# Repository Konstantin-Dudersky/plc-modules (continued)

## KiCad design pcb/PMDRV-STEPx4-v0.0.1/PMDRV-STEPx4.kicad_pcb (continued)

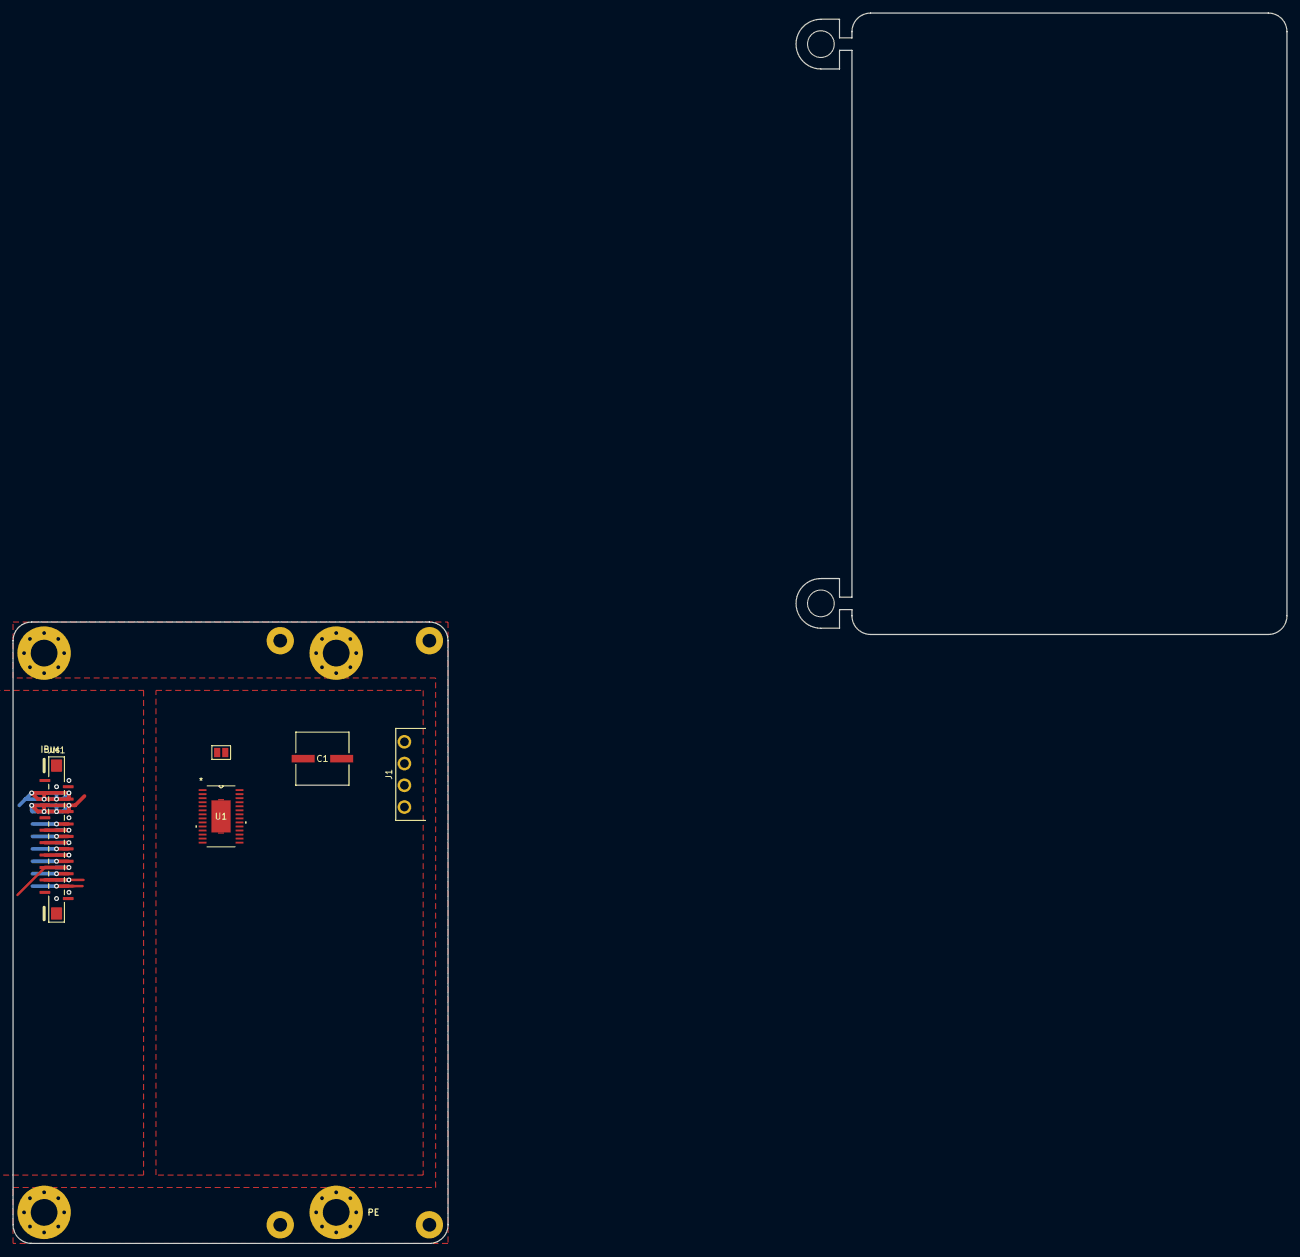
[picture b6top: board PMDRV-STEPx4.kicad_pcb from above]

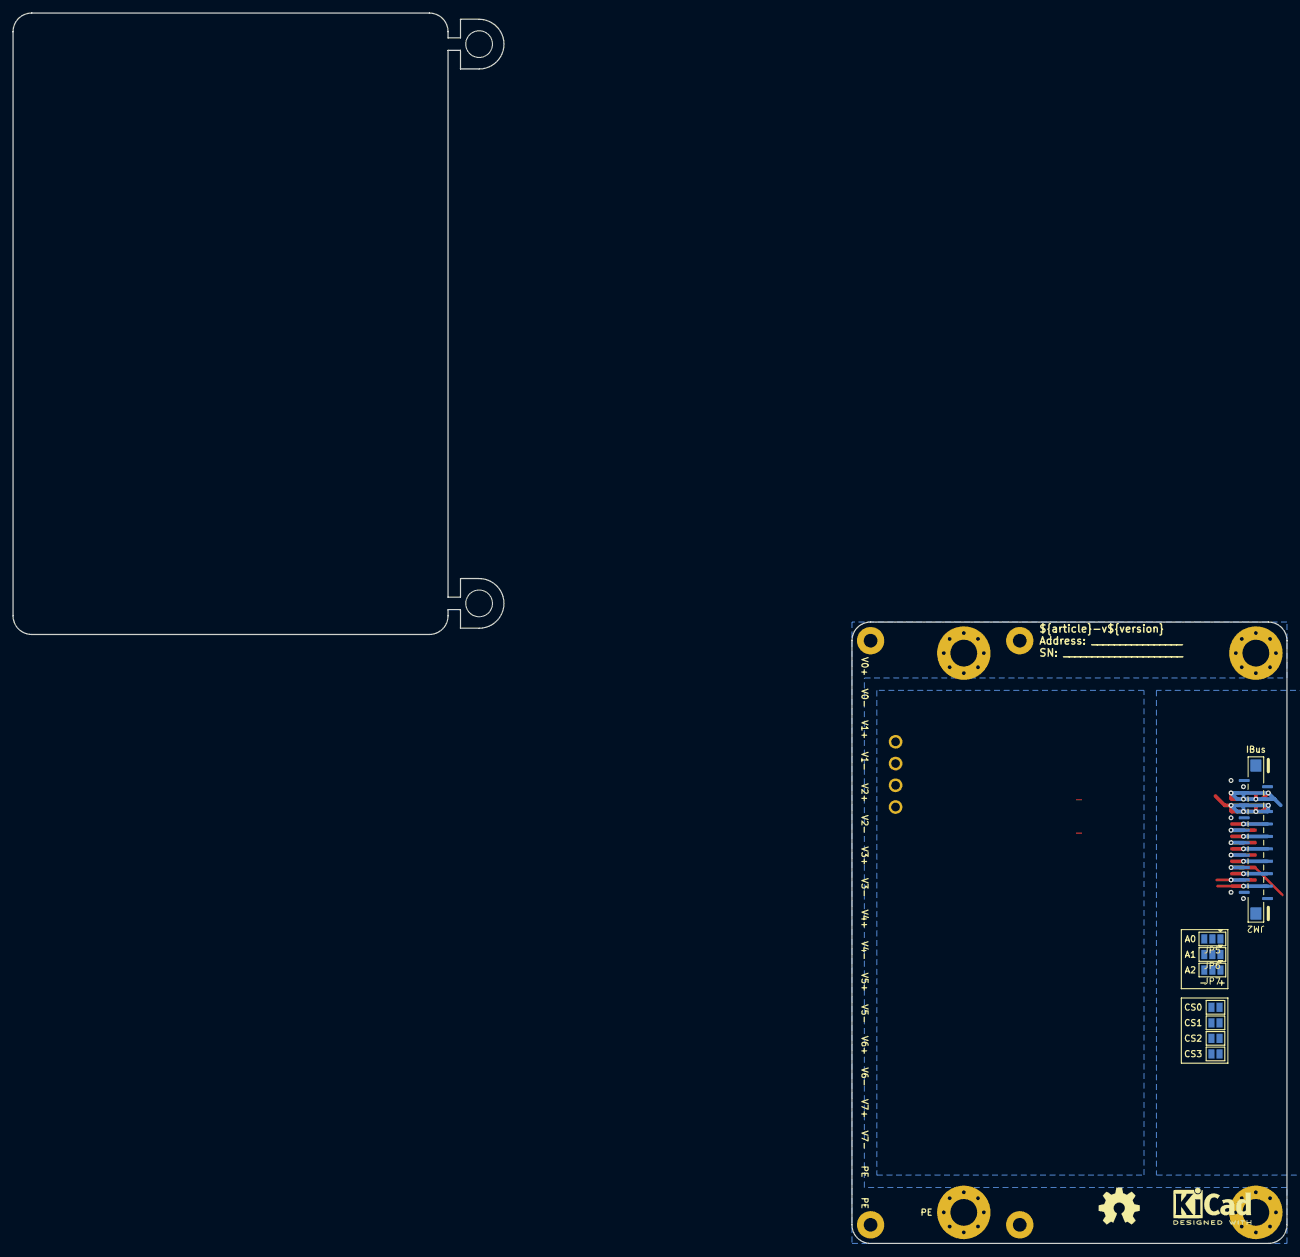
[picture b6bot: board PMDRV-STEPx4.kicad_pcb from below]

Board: 2 copper layers, 70.0 x 100.0 mm, 20 parts (10 on the bottom side), 15 nets.

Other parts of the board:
kicad_logo: KiCad-Logo2_5mm_SilkScreen
oshw_logo: OSHW-Symbol_6.7x6mm_SilkScreen

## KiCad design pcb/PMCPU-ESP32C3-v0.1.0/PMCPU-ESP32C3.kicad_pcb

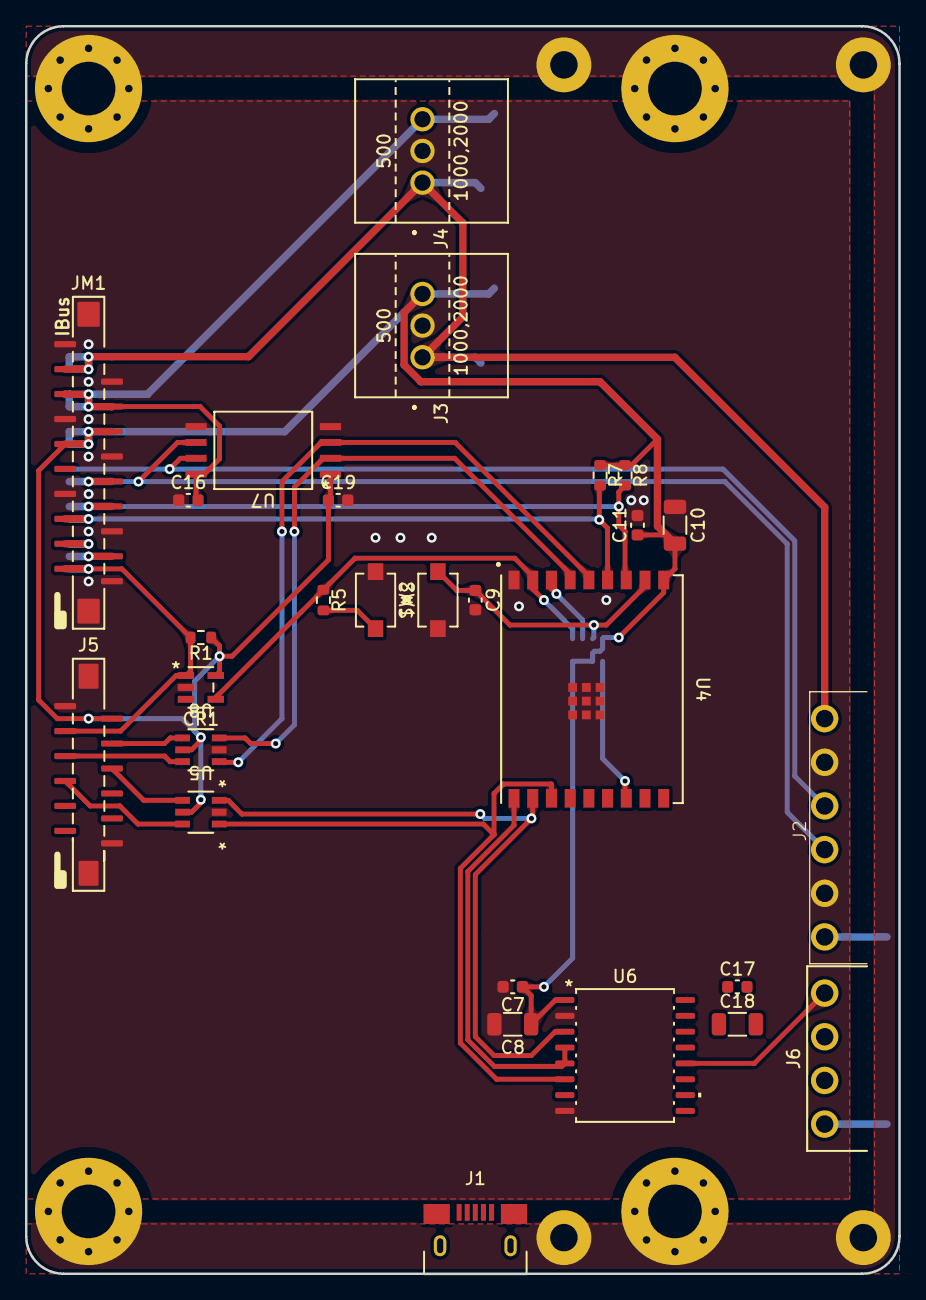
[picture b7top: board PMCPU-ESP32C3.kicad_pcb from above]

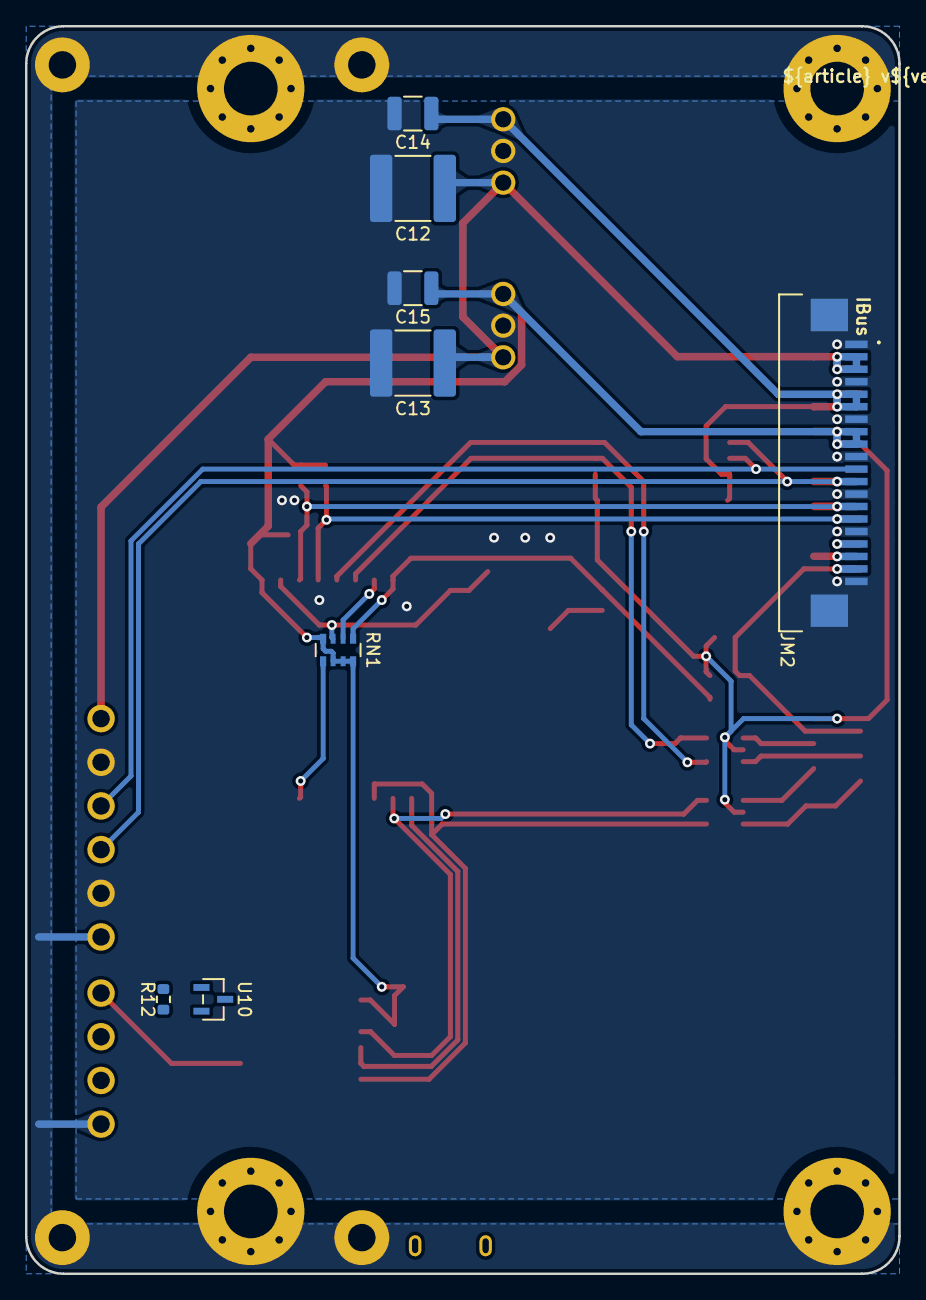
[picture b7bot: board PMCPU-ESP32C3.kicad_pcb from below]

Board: 2 copper layers, 70.0 x 100.0 mm, 43 parts (10 on the bottom side), 32 nets.

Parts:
C7, C16, C17, C19: 100nF; C_0603_1608Metric
C8, C10, C18: 10uF; C_1206_3216Metric
C9, C11: 1uF; C_0603_1608Metric
C12, C13: 22uF; C_2220_5750Metric
C14, C15: 22uF; C_1210_3225Metric
CR1: STWD100NYWY3F; SOT23-5L_STM
H1, H2, H3, H4: M4; MountingHole_4.3mm_M4_Pad_Via
J1: U254-051T-4BH83-S1S; CONN5_H83-S1S_XKB
J2: 15EDGRC-3.5-06P
J3: K7803-2000R3; K7805-2000R3
J4: K7805-2000R3
J5: AFA11-S12GLA-00
J6: 15EDGRC-3.5-04P
JM1: AFA07-S20FCC-00; AFA11-S20GLA-00
JM2: AFA07-S20FCC-00; AFA07S20FCA00
R1: 10k; R_0603_1608Metric
R5: 330R; R_0603_1608Metric
R7, R8: 3k3; R_0603_1608Metric
R12: 120R; R_0603_1608Metric
RN1: 10k; R_Array_Convex_4x0603
SP1: PMLED-xx-v0.0.3
SW1, SW2: Button; SW_TS-1088_XNP-M
U4: ESP32-C3-WROOM-02U-N4; ESP32-C3-WROOM-02U_EXP
U5, U8: SN74LVC2G14DBVR; DBV6-M
U6: CA-IS3098W; SOIC16-WBW_CLG
U7: CA-IS3050G; SOIC8_CA-IS305_CLG
U10: CDSOT23-SM712; SOT_SM712
kicad_logo: KiCad-Logo2_5mm_SilkScreen
oshw_logo: OSHW-Symbol_6.7x6mm_SilkScreen

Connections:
+3.3V_EXT_RS485: C17.1, C18.1, U6.16 (VISO)
/CAN_RX: U4.6 (IO7), U7.2 (RXD), U8.3 (2A)
/CAN_RX_LED: J5.4, U8.4 (2Y)
/CAN_TX: U4.5 (IO6), U7.3 (TXD), U8.1 (1A)
/CAN_TX_LED: J5.5, U8.6 (1Y)
/EN: C9.1, RN1.3 (R3.1), SW2.2, U4.2 (EN)
/IBUS_CAN_H: J2.4, JM1.11, JM2.11, U7.7 (CANH)
/IBUS_CAN_L: J2.3, JM1.12 (Pin_11), JM2.12 (Pin_11), U7.6 (CANL)
/IBUS_I2C_SCL: JM1.15 (Pin_11), JM2.15 (Pin_11), R7.2, U4.4 (IO5)
/IBUS_I2C_SDA: JM1.14 (Pin_11), JM2.14 (Pin_11), R8.2, U4.3 (IO4)
/IBUS_RST: CR1.1 (*WDO), J5.3, JM1.19 (Pin_11), JM2.19 (Pin_11), R1.2
/RS485-A: J6.4, R12.2, U6.12 (A), U10.1
/RS485-B: J6.3, R12.1, U6.13 (B), U10.2
/UART_RTS: U4.10 (IO10), U6.4 (RE), U6.5 (DE)
/UART_RX: U4.11 (RXD_(IO20)), U5.3 (2A), U6.3 (RO)
/UART_RX_LED: J5.6, U5.4 (2Y)
/UART_TX: U4.12 (TXD_(IO21)), U5.1 (1A), U6.6 (DI)
/UART_TX_LED: J5.7, U5.6 (1Y)
/USB_D+: J1.3 (D+), U4.14 (IO19_(USB_D+))
/USB_D-: J1.2 (D-), U4.13 (IO18_(USB_D-))
/WDT: CR1.4 (WDI), R5.1, RN1.1 (R1.1), U4.8 (IO9)
GND_EXT_RS485: C17.2, C18.2, J6.2, U6.9 (GNDB), U6.10 (SEL), U6.15 (GNDB), U10.3
IBUS_3V3: C7.1, C8.1, C10.2, C11.1, C15.1, C19.1, CR1.5 (VCC), J3.3 (+VO), J5.2, JM1.8, JM1.9, JM2.8, JM2.9, R1.1, R7.1, R8.1, RN1.4 (R4.1), RN1.6 (R3.2), RN1.7 (R2.2), RN1.8 (R1.2), U4.1 (3V3), U5.5 (VCC), U6.1 (VDD), U7.1 (VCC1), U8.5 (VCC)
IBUS_5V: C14.1, C16.2, J4.3 (+VO), JM1.5, JM1.6, JM2.5, JM2.6, U7.8 (VCC2)
IBUS_24V: C12.1, C13.1, J2.6, J3.1 (VIN), J4.1 (VIN), JM1.2, JM1.3, JM2.2, JM2.3
IBUS_CAN_GND: C7.2, C8.2, C9.2, C10.1, C11.2, C12.2, C13.2, C14.2, C15.2, C16.1, C19.2, CR1.2 (GND), J1.5 (GND), J2.2, J2.5, J3.2 (GND), J4.2 (GND), J5.1, J5.12 (Pin_11), J5.MP1 (Pin_11), J5.MP2 (Pin_11), JM1.1, JM1.4, JM1.7, JM1.10, JM1.13 (Pin_11), JM1.16 (Pin_11), JM1.20 (Pin_11), JM1.MP1 (Pin_11), JM1.MP2 (Pin_11), JM2.1, JM2.4, JM2.7, JM2.10, JM2.13 (Pin_11), JM2.16 (Pin_11), JM2.20 (Pin_11), JM2.MP1 (Pin_11), JM2.MP2 (Pin_11), SW1.1, SW2.1, U4.9 (GND), U4.EPAD, U5.2 (GND), U6.2 (GNDA), U6.8 (GNDA), U7.4 (GND1), U7.5 (GND2), U8.2 (GND)
unnamed: JM1.17 (Pin_11), JM2.17 (Pin_11)
unnamed: JM1.18 (Pin_11), JM2.18 (Pin_11)
unnamed: R5.2, SW1.2
unnamed: RN1.2 (R2.1), U4.7 (IO8)
unnamed: RN1.5 (R4.2), U4.16 (IO2)
PE: H1.1 (1_1), H2.1 (1_1), H3.1 (1_1), H4.1 (1_1), J2.1, J6.1, SP1.PE (PE_PE)

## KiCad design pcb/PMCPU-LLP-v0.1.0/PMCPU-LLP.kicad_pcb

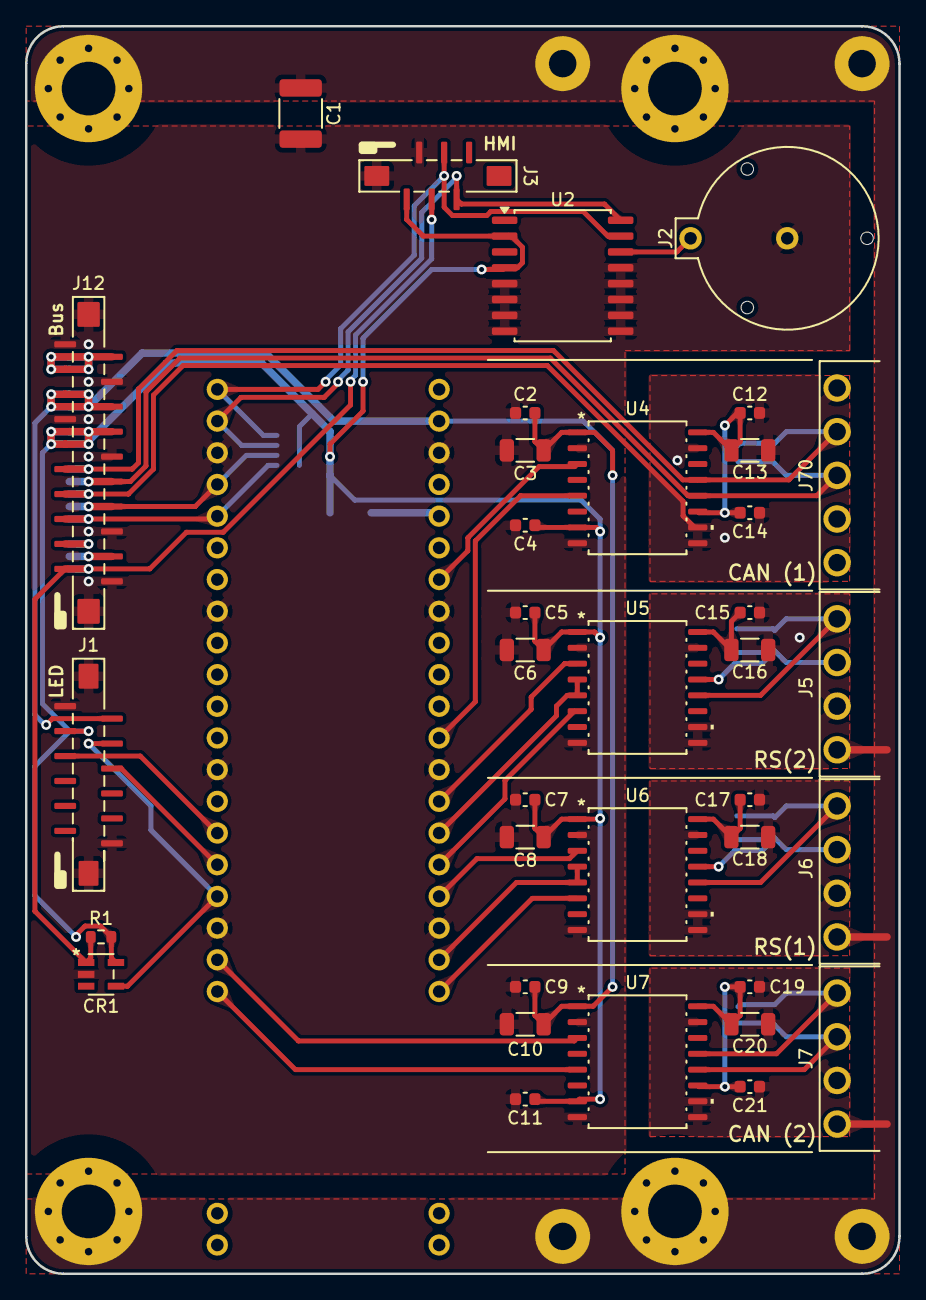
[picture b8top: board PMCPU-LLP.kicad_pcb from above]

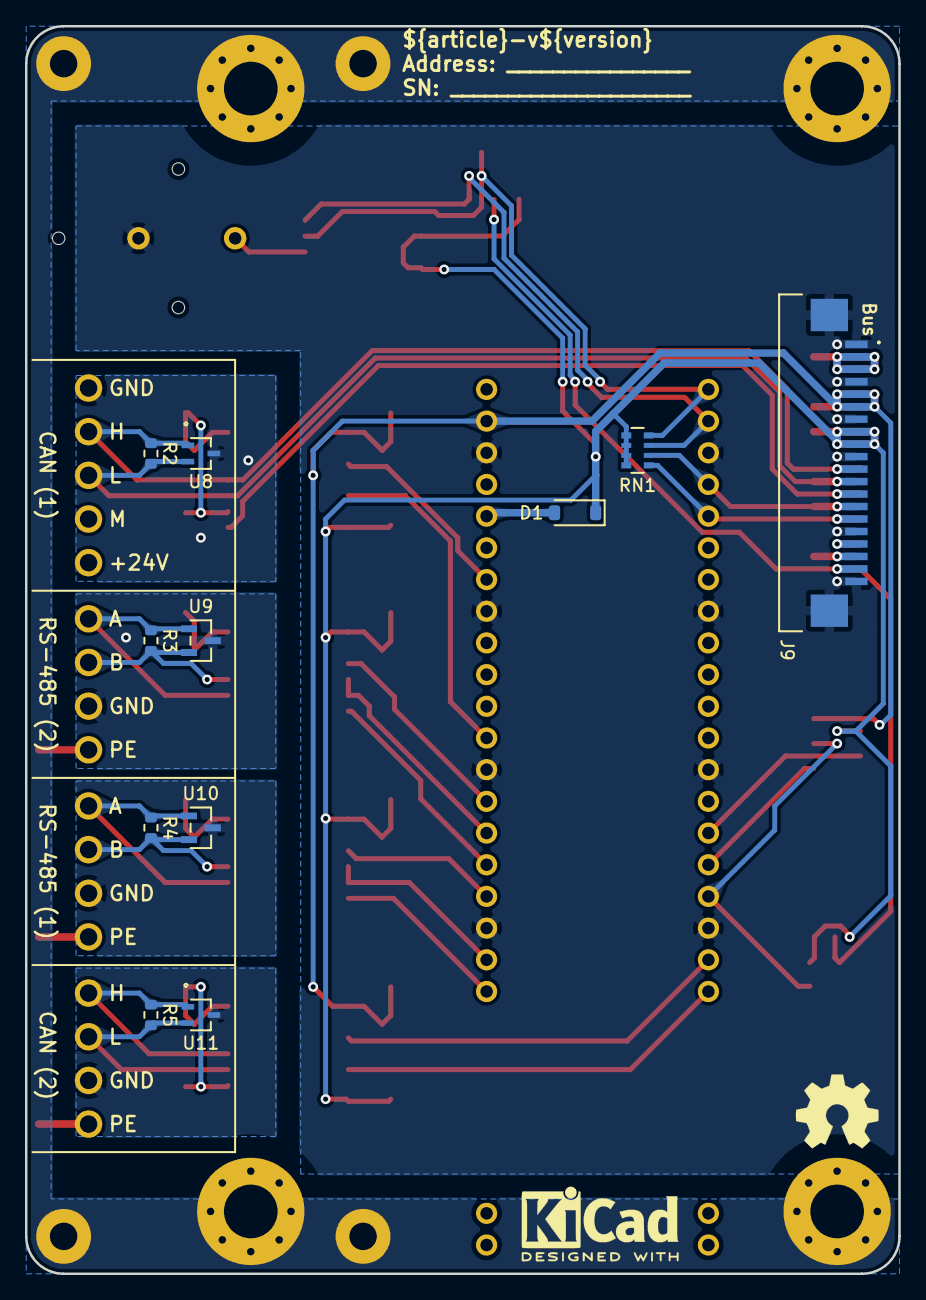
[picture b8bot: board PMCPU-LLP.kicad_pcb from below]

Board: 2 copper layers, 70.0 x 100.0 mm, 55 parts (13 on the bottom side), 43 nets.

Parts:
C1: 4.7nF 2kV; C_1812_4532Metric
C2, C5, C7, C9, C12, C15, C17, C19: 100nF; C_0603_1608Metric
C3, C6, C8, C10, C13, C16, C18, C20: 10uF; C_1206_3216Metric
C4, C11, C14, C21: 1uF; C_0603_1608Metric
CR1: STWD100NYWY3F; SOT23-5L_STM
D1: B5819W; D_SOD-123
H1, H2, H3, H4: M4; MountingHole_4.3mm_M4_Pad_Via
J1: AFA07-S10FCC-00; AFA11-S12GLA-00
J2: BS-12-A1AJ002-F
J3: AFA11-S06GLA-00
J5, J6, J7: 15EDGRC-3.5-04P
J9: AFA07-S20FCC-00; AFA07S20FCA00
J12: AFA11-S20GLA-00
J70: 15EDGRC-3.5-05P
R1: 10k; R_0603_1608Metric
R2, R3, R4, R5: 120R; R_0603_1608Metric
RN1: 3k3; R_Array_Convex_4x0603
SP1: PMLED-xx-v0.0.3
U2: DS3231; SOIC-16W_7.5x10.3mm_P1.27mm
U3: LuckfoxLyraPlus
U4, U7: CA-IS3062VW; SOIC16-WBW_CLG
U5, U6: CA-IS3098W; SOIC16-WBW_CLG
U8, U11: ESDCAN05-2BWY; SOT323-3L_STM
U9, U10: CDSOT23-SM712; SOT_SM712
kicad_logo0: KiCad-Logo2_5mm_SilkScreen
oshw_logo: OSHW-Symbol_6.7x6mm_SilkScreen

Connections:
+3.3V_CPU: C4.1, C5.1, C6.1, C7.1, C8.1, C11.1, CR1.5 (VCC), D1.1 (K), J1.3, J3.6, J9.8, J9.9, J12.8, J12.9, R1.1, RN1.5 (R4.2), RN1.6 (R3.2), RN1.7 (R2.2), RN1.8 (R1.2), U2.2 (VCC), U2.4 (~RST), U4.7 (Vccl), U5.1 (VDD), U6.1 (VDD), U7.7 (Vccl)
+3.3V_EXT_RS485_1: C17.1, C18.1, U6.16 (VISO)
+3.3V_EXT_RS485_2: C15.1, C16.1, U5.16 (VISO)
+5V_CPU: C2.1, C3.1, C9.1, C10.1, J1.2, J9.5, J9.6, J12.5, J12.6, U3.39 (VSYS), U4.1 (Vcc), U7.1 (Vcc)
+5V_EB: C19.1, C20.1, C21.1, U7.11 (Visoin), U7.16 (Viso)
+24V_CPU: J9.2, J9.3, J12.2, J12.3
/CAN0_RXD: U3.20 (RM_IO2), U7.5 (RXD)
/CAN0_TXD: U3.19 (RM_IO3), U7.3 (TXD)
/CAN1_RXD: U3.29 (RM_IO25), U4.5 (RXD)
/CAN1_TXD: U3.34 (RM_IO24), U4.3 (TXD)
/CANH_EB: J7.4, R5.1, U7.13 (CANH), U11.1
/CANL_EB: J7.3, R5.2, U7.12 (CANL), U11.2
/I2C1_SCL: J3.2, RN1.3 (R3.1), U2.16 (SCL), U3.2 (RM_IO23)
/I2C1_SDA: J3.3, RN1.4 (R4.1), U2.15 (SDA), U3.1 (RM_IO22)
/IBUS_CAN_GND: C12.2, C13.2, C14.2, J9.13 (Pin_11), J12.13 (Pin_11), J70.5, U4.9 (GND2), U4.10 (GND2), U4.15 (GND2), U8.3
/IBUS_CAN_H: J9.11, J12.11, J70.4, R2.1, U4.13 (CANH), U8.1
/IBUS_CAN_L: J9.12 (Pin_11), J12.12 (Pin_11), J70.3, R2.2, U4.12 (CANL), U8.2
/IBUS_I2C_SCL: J9.15 (Pin_11), J12.15 (Pin_11), RN1.1 (R1.1), U3.5 (RM_IO13)
/IBUS_I2C_SDA: J9.14 (Pin_11), J12.14 (Pin_11), RN1.2 (R2.1), U3.4 (RM_IO12)
/IBUS_RST: CR1.1 (*WDO), J3.4, J9.19 (Pin_11), J12.19 (Pin_11), R1.2
/LED_0: J1.5, U3.15 (RM_IO6)
/LED_1: J1.6, U3.16 (RM_IO5)
/RS485_1-A: J6.4, R4.2, U6.12 (A), U10.1
/RS485_1-B: J6.3, R4.1, U6.13 (B), U10.2
/RS485_2-A: J5.4, R3.2, U5.12 (A), U9.1
/RS485_2-B: J5.3, R3.1, U5.13 (B), U9.2
/UART1_RTS: U3.22 (RM_IO30), U6.4 (RE), U6.5 (DE)
/UART1_RX: U3.24 (RM_IO29), U6.3 (RO)
/UART1_TX: U3.21 (RM_IO31), U6.6 (DI)
/UART2_RTS: U3.26 (RM_IO27), U5.4 (RE), U5.5 (DE)
/UART2_RX: U3.27 (RM_IO26), U5.3 (RO)
/UART2_TX: U3.25 (RM_IO28), U5.6 (DI)
/Vbat: J2.1, U2.14 (VBAT)
/WDT: CR1.4 (WDI), J1.4, U3.17 (RM_IO4)
GND_CPU: C1.2, C2.2, C3.2, C4.2, C5.2, C6.2, C7.2, C8.2, C9.2, C10.2, C11.2, CR1.2 (GND), J1.1, J1.12 (Pin_11), J1.MP1 (Pin_11), J1.MP2 (Pin_11), J2.2, J3.5, J3.MP2 (Pin_11), J9.1, J9.4, J9.7, J9.10, J9.16 (Pin_11), J9.20 (Pin_11), J9.MP1 (Pin_11), J9.MP2 (Pin_11), J12.1, J12.4, J12.7, J12.10, J12.16 (Pin_11), J12.20 (Pin_11), J12.MP1 (Pin_11), J12.MP2 (Pin_11), U2.5 (GND), U2.6 (GND), U2.7 (GND), U2.8 (GND), U2.9 (GND), U2.10 (GND), U2.11 (GND), U2.12 (GND), U2.13 (GND), U3.3 (GND), U3.8 (GND), U3.13 (GND), U3.18 (GND), U3.23 (GND), U3.28 (GND), U3.33 (GND), U3.38 (GND), U4.2 (GND1), U4.8 (GND1), U5.2 (GNDA), U5.8 (GNDA), U6.2 (GNDA), U6.8 (GNDA), U7.2 (GND1), U7.8 (GND1)
GND_EB: C19.2, C20.2, C21.2, J7.2, U7.9 (GND2), U7.10 (GND2), U7.15 (GND2), U11.3
GND_EXT_RS485_1: C17.2, C18.2, J6.2, U6.9 (GNDB), U6.10 (SEL), U6.15 (GNDB), U10.3
GND_EXT_RS485_2: C15.2, C16.2, J5.2, U5.9 (GNDB), U5.10 (SEL), U5.15 (GNDB), U9.3
unnamed: D1.2 (A), U3.36 (3V3_OUT)
unnamed: J9.17 (Pin_11), J12.17 (Pin_11)
unnamed: J9.18 (Pin_11), J12.18 (Pin_11)
unnamed: C12.1, C13.1, C14.1, U4.11 (Visoin), U4.16 (Viso)
PE: C1.1, H1.1 (1_1), H2.1 (1_1), H3.1 (1_1), H4.1 (1_1), J5.1, J6.1, J7.1, SP1.PE (PE_PE)

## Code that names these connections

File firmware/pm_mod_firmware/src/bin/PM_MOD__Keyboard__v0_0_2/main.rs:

use std::time::Duration;

use esp_idf_svc::hal::{gpio::AnyIOPin, prelude::Peripherals};
use rsiot::{
    components::cmp_esp_spi_master,
    executor::{ComponentExecutor, ComponentExecutorConfig},
    logging::configure_logging,
};
use tokio::task::LocalSet;
use tracing::level_filters::LevelFilter;

use pm_mod_firmware::define_address;

mod config_esp_spi_master;
mod config_esp_uart_slave;
mod config_logger;
mod message;

use message::*;

#[tokio::main(flavor = "current_thread")]
async fn main() -> anyhow::Result<()> {
    esp_idf_svc::sys::link_patches();

    configure_logging(LevelFilter::INFO).unwrap();

    let peripherals = Peripherals::take().unwrap();

    // Периферия ESP -------------------------------------------------------------------------------
    let spi = peripherals.spi2;
    let mut pin_mosi: AnyIOPin = peripherals.pins.gpio0.into();
    let mut pin_miso: AnyIOPin = peripherals.pins.gpio1.into();
    let mut pin_sck: AnyIOPin = peripherals.pins.gpio3.into();
    let pin_cs0 = peripherals.pins.gpio10;
    let pin_cs1 = peripherals.pins.gpio2;

    let uart = peripherals.uart1;
    let pin_uart_rx = peripherals.pins.gpio20;
    let pin_uart_tx = peripherals.pins.gpio21;
    let pin_uart_rts = peripherals.pins.gpio4;

    // UART address --------------------------------------------------------------------------------
    let uart_slave_address = define_address(&mut pin_mosi, &mut pin_miso, &mut pin_sck);

    // cmp_esp_spi_master --------------------------------------------------------------------------
    let config_esp_spi_master = config_esp_spi_master::config(
        spi,
        pin_mosi,
        pin_miso,
        pin_sck,
        pin_cs0.into(),
        pin_cs1.into(),
    );

    // executor ------------------------------------------------------------------------------------
    let executor_config = ComponentExecutorConfig {
        buffer_size: 50,
        fn_auth: |msg, _| Some(msg),
        delay_publish: Duration::from_millis(100),
    };

    let local_set = LocalSet::new();
    local_set.spawn_local(async move {
        ComponentExecutor::<MRoot>::new(executor_config)
            .add_cmp(config_esp_uart_slave::cmp(
                uart_slave_address,
                uart,
                pin_uart_rx.into(),
                pin_uart_tx.into(),
                pin_uart_rts.into(),
            ))
            .add_cmp(cmp_esp_spi_master::Cmp::new(config_esp_spi_master))
            .add_cmp(config_logger::cmp())
            .wait_result()
            .await
            .unwrap()
    });
    local_set.await;

    Ok(())
}

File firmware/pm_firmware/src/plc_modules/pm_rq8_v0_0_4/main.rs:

use std::time::Duration;

use esp_idf_svc::hal::{gpio::AnyIOPin, prelude::Peripherals};
use rsiot::{
    components::{cmp_esp_spi_master, cmp_esp_uart_slave, cmp_logger},
    executor::{ComponentExecutor, ComponentExecutorConfig},
};
use tokio::task::LocalSet;

use pm_firmware_uart_shared::settings::MESSAGE_LEN;

use crate::{define_address, service::Service};

use super::Custom;

pub async fn main() -> anyhow::Result<()> {
    let peripherals = Peripherals::take().unwrap();

    // Периферия ESP -------------------------------------------------------------------------------
    let spi = peripherals.spi2;
    let mut pin_mosi: AnyIOPin = peripherals.pins.gpio4.into();
    let mut pin_miso: AnyIOPin = peripherals.pins.gpio5.into();
    let mut pin_sck: AnyIOPin = peripherals.pins.gpio6.into();
    let pin_cs_gpio_output = peripherals.pins.gpio8;

    let uart = peripherals.uart1;
    let pin_uart_rx = peripherals.pins.gpio20;
    let pin_uart_tx = peripherals.pins.gpio21;
    let pin_uart_rts = peripherals.pins.gpio10;

    // I2C address ---------------------------------------------------------------------------------
    let slave_address = define_address(20, &mut pin_mosi, &mut pin_miso, &mut pin_sck);

    // cmp_esp_uart_slave --------------------------------------------------------------------------
    let config_esp_uart_slave = super::config_esp_uart_slave::config::<_, _, MESSAGE_LEN>(
        slave_address,
        uart,
        pin_uart_rx.into(),
        pin_uart_tx.into(),
        pin_uart_rts.into(),
    );

    // cmp_esp_spi_master --------------------------------------------------------------------------
    let config_esp_spi_master = super::config_esp_spi_master::config(
        spi,
        pin_mosi,
        pin_miso,
        pin_sck,
        pin_cs_gpio_output.into(),
    );

    // cmp_logger ----------------------------------------------------------------------------------
    let config_logger = super::config_logger::config();

    // executor ------------------------------------------------------------------------------------
    let executor_config = ComponentExecutorConfig {
        buffer_size: 50,
        service: Service::PM_RQ8,
        fn_auth: |msg, _| Some(msg),
        delay_publish: Duration::from_millis(100),
    };

    let local_set = LocalSet::new();
    local_set.spawn_local(async {
        ComponentExecutor::<Custom, Service>::new(executor_config)
            .add_cmp(cmp_esp_uart_slave::Cmp::new(config_esp_uart_slave))
            .add_cmp(cmp_esp_spi_master::Cmp::new(config_esp_spi_master))
            .add_cmp(cmp_logger::Cmp::new(config_logger))
            .wait_result()
            .await
            .unwrap()
    });
    local_set.await;

    Ok(())
}

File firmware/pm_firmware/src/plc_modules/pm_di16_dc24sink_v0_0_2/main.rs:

use std::time::Duration;

use esp_idf_svc::hal::prelude::Peripherals;
use rsiot::{
    components::{cmp_derive, cmp_esp_gpio, cmp_esp_i2c_slave, cmp_esp_spi_master, cmp_logger},
    executor::{ComponentExecutor, ComponentExecutorConfig},
};
use tokio::task::LocalSet;

use crate::{define_address, service::Service};

use super::Custom;

pub async fn main() -> anyhow::Result<()> {
    let peripherals = Peripherals::take().unwrap();

    // Периферия ESP -------------------------------------------------------------------------------
    let i2c = peripherals.i2c0;
    let spi = peripherals.spi2;

    let pin_a0 = peripherals.pins.gpio21;
    let pin_a1 = peripherals.pins.gpio20;
    let pin_a2 = peripherals.pins.gpio10;

    let pin_sda = peripherals.pins.gpio0;
    let pin_scl = peripherals.pins.gpio1;

    let pin_mosi = peripherals.pins.gpio2;
    let pin_miso = peripherals.pins.gpio3;
    let pin_sck = peripherals.pins.gpio9;
    let pin_cs_gpio_input = peripherals.pins.gpio8;
    let pin_cs_gpio_led = peripherals.pins.gpio7;
    let pin_int_gpio_expander = peripherals.pins.gpio6;

    // I2C address ---------------------------------------------------------------------------------
    let slave_address = define_address(
        10,
        &mut pin_a0.into(),
        &mut pin_a1.into(),
        &mut pin_a2.into(),
    );

    // cmp_derive ----------------------------------------------------------------------------------
    let config_derive = super::config_derive::config();

    // cmp_esp_gpio --------------------------------------------------------------------------------
    let config_esp_gpio = super::config_esp_gpio::config(pin_int_gpio_expander.into());

    // cmp_esp_i2c_slave ---------------------------------------------------------------------------
    let config_esp_i2c_slave =
        super::config_esp_i2c_slave::config(i2c, pin_sda.into(), pin_scl.into(), slave_address);

    // cmp_esp_spi_master --------------------------------------------------------------------------
    let config_esp_spi_master = super::config_esp_spi_master::config(
        spi,
        pin_mosi.into(),
        pin_miso.into(),
        pin_sck.into(),
        pin_cs_gpio_input.into(),
        pin_cs_gpio_led.into(),
    );

    // cmp_logger ----------------------------------------------------------------------------------
    let config_logger = super::config_logger::config();

    // executor ------------------------------------------------------------------------------------
    let executor_config = ComponentExecutorConfig {
        buffer_size: 50,
        service: Service::PM_DI16,
        fn_auth: |msg, _| Some(msg),
        delay_publish: Duration::from_millis(100),
    };

    let local_set = LocalSet::new();
    local_set.spawn_local(async {
        ComponentExecutor::<Custom, Service>::new(executor_config)
            .add_cmp(cmp_logger::Cmp::new(config_logger))
            .add_cmp(cmp_derive::Cmp::new(config_derive))
            .add_cmp(cmp_esp_i2c_slave::Cmp::new(config_esp_i2c_slave))
            .add_cmp(cmp_esp_spi_master::Cmp::new(config_esp_spi_master))
            .add_cmp(cmp_esp_gpio::Cmp::new(config_esp_gpio))
            .wait_result()
            .await
            .unwrap()
    });
    local_set.await;

    Ok(())
}

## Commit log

2024-04-20 init
2024-04-22 DI16
2024-04-23 breadboard for DI8
2024-04-23 sync
2024-04-23 power source
2024-05-06 PM-GE16
2024-05-06 PM-ADC4
2024-05-06 PM-OC08
2024-05-07 PM-Front-DI16
2024-05-08 rename
2024-05-08 add files
2024-05-13 PM-R4
2024-05-16 PM-Front-DI8
2024-05-17 change .gitignore
2024-05-27 PM-RQ8
2024-05-29 PM_DI16-front-DC24
2024-05-30 PM-DI16-base
2024-05-30 v0.0.1 send to nextpcb
2024-06-07 models
2024-06-11 update step files
2024-06-24 v0.0.1
2024-06-24 fix PC817 footprint
2024-06-24 work on v0.0.2
2024-06-25 v0.0.2
2024-06-25 PM-CPU-RP
2024-06-26 send to nextpcb
2024-07-01 PM-CPU-ESP
2024-07-01 archive v0.0.2
2024-07-02 PM-CPU-ESP-front
2024-07-10 calculation
2024-07-11 add docs
2024-07-11 docs
2024-07-12 docs updated
2024-07-14 PM_Bus
2024-07-15 InvenTree
2024-07-15 PM-RQ-front - InvenTree
2024-07-15 Start PM-AI-IU4
2024-07-16 PM-AU-IU4
2024-07-16 PM-AI8-IU
2024-07-17 Work on PM-AI8-IU
2024-07-19 PM-AI8-IU-front
2024-07-22 PM-AI-xxx docs
2024-07-24 PM-AI8-I start
2024-07-28 PM-AI1-W
2024-07-31 PM-DI16-DC24sink
2024-08-01 PM-AI8-I
2024-08-02 PM-AI8-U
2024-08-05 PM-PS
2024-08-06 PM-ESPC3
2024-08-07 PM-DI16
2024-08-12 add version numbers
2024-08-27 step
2024-08-29 update ESPC3
2024-09-09 create firmware project
2024-09-10 firmware
2024-09-11 fix errors
2024-09-13 move to rsiot
2024-09-16 update to rsiot
2024-09-18 Update PM_RQ8__v0_0_3
2024-09-22 update toolchain
2024-09-23 new PM-RQ8
2024-09-23 PM-Led
2024-09-24 add i2c delay
2024-09-25 PM-DI24sink
2024-09-25 Update PM_DI16_DC24sink__v0_0_2
2024-09-27 PM-LED16
2024-09-27 PM-LED8
2024-10-22 PM-Keyboard
2024-10-22 PM-Debug
2024-10-23 export
2024-10-24 main
2024-10-25 update new size
2024-11-23 update PM-RP
2024-12-15 new version
2025-01-15 zip old plates
2025-02-09 PM_CNV-AI8_IU
2025-02-22 before v9
2025-02-23 PM_DBG
2025-02-27 PM_CNV-AI4_W-v0.0.2
2025-03-02 PM_HMI-Touch
2025-03-05 nextpcb order
2025-03-05 deelte embuild
2025-03-08 update docs
2025-03-09 setup new files
2025-03-12 remove pagebreak level 2
2025-03-13 setup fonts
2025-05-29 PM-CPU_LLU
2025-06-14 add i2c
2025-06-19 PMCNV-RQ8
2025-06-19 PMCNV-DQ16src
2025-07-10 order nextpcb
2026-04-01 order
2026-05-12 add PMCMV_PWMx16_v000001
2026-05-13 INA226 firmware
2026-05-19 new order
2026-06-10 new structure
2026-06-11 DIx32
2026-06-11 DQx16
2026-06-11 RQx8
2026-06-11 PMPS-20W
